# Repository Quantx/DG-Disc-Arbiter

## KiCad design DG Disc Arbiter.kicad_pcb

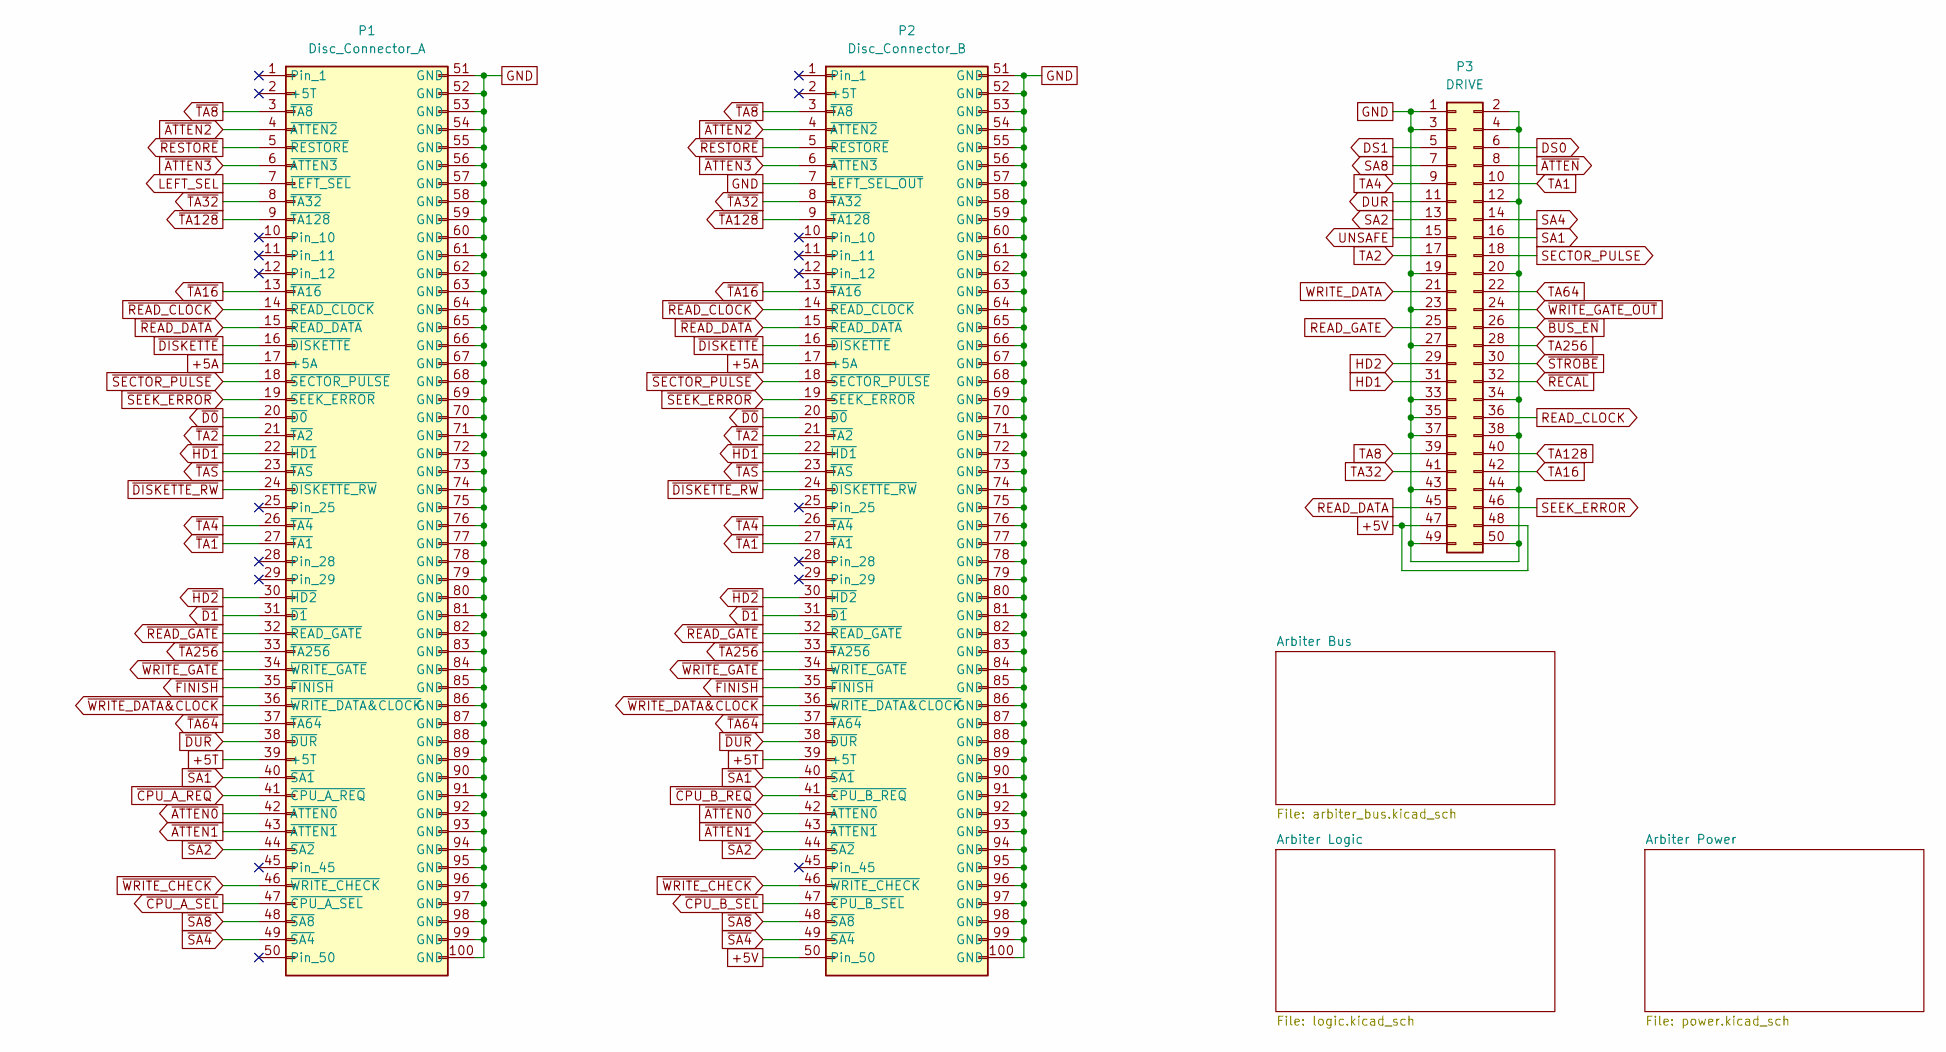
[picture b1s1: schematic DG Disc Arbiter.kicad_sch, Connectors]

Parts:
P1: Disc_Connector_A
P2: Disc_Connector_B
P3: DRIVE

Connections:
unnamed: P1.3 (~TA8), P2.3 (~TA8)
unnamed: P1.4 (~ATTEN2), P2.4 (~ATTEN2)
unnamed: P1.5 (~RESTORE), P2.5 (~RESTORE)
unnamed: P1.6 (~ATTEN3), P2.6 (~ATTEN3)
unnamed: P1.8 (~TA32), P2.8 (~TA32)
unnamed: P1.9 (~TA128), P2.9 (~TA128)
unnamed: P1.13 (~TA16), P2.13 (~TA16)
unnamed: P1.14 (~READ_CLOCK), P2.14 (~READ_CLOCK)
unnamed: P1.15 (~READ_DATA), P2.15 (~READ_DATA)
unnamed: P1.16 (~DISKETTE), P2.16 (~DISKETTE)
unnamed: P1.17 (+5A), P2.17 (+5A)
unnamed: P1.18 (~SECTOR_PULSE), P2.18 (~SECTOR_PULSE)
unnamed: P1.19 (~SEEK_ERROR), P2.19 (~SEEK_ERROR)
unnamed: P1.20 (~D0), P2.20 (~D0)
unnamed: P1.21 (~TA2), P2.21 (~TA2)
unnamed: P1.22 (~HD1), P2.22 (~HD1)
unnamed: P1.23 (~TAS), P2.23 (~TAS)
unnamed: P1.24 (~DISKETTE_RW), P2.24 (~DISKETTE_RW)
unnamed: P1.26 (~TA4), P2.26 (~TA4)
unnamed: P1.27 (~TA1), P2.27 (~TA1)
unnamed: P1.30 (~HD2), P2.30 (~HD2)
unnamed: P1.31 (~D1), P2.31 (~D1)
unnamed: P1.32 (~READ_GATE), P2.32 (~READ_GATE)
unnamed: P1.33 (~TA256), P2.33 (~TA256)
unnamed: P1.34 (~WRITE_GATE), P2.34 (~WRITE_GATE)
unnamed: P1.35 (~FINISH), P2.35 (~FINISH)
unnamed: P1.36 (~WRITE_DATA&CLOCK), P2.36 (~WRITE_DATA&CLOCK)
unnamed: P1.37 (~TA64), P2.37 (~TA64)
unnamed: P1.38 (~DUR), P2.38 (~DUR)
unnamed: P1.39 (+5T), P2.39 (+5T)
unnamed: P1.40 (~SA1), P2.40 (~SA1)
unnamed: P1.42 (~ATTEN0), P2.42 (~ATTEN0)
unnamed: P1.43 (~ATTEN1), P2.43 (~ATTEN1)
unnamed: P1.44 (~SA2), P2.44 (~SA2)
unnamed: P1.46 (~WRITE_CHECK), P2.46 (~WRITE_CHECK)
unnamed: P1.48 (~SA8), P2.48 (~SA8)
unnamed: P1.49 (~SA4), P2.49 (~SA4)
unnamed: P1.51 (GND), P1.52 (GND), P1.53 (GND), P1.54 (GND), P1.55 (GND), P1.56 (GND), P1.57 (GND), P1.58 (GND), P1.59 (GND), P1.60 (GND), P1.61 (GND), P1.62 (GND), P1.63 (GND), P1.64 (GND), P1.65 (GND), P1.66 (GND), P1.67 (GND), P1.68 (GND), P1.69 (GND), P1.70 (GND), P1.71 (GND), P1.72 (GND), P1.73 (GND), P1.74 (GND), P1.75 (GND), P1.76 (GND), P1.77 (GND), P1.78 (GND), P1.79 (GND), P1.80 (GND), P1.81 (GND), P1.82 (GND), P1.83 (GND), P1.84 (GND), P1.85 (GND), P1.86 (GND), P1.87 (GND), P1.88 (GND), P1.89 (GND), P1.90 (GND), P1.91 (GND), P1.92 (GND), P1.93 (GND), P1.94 (GND), P1.95 (GND), P1.96 (GND), P1.97 (GND), P1.98 (GND), P1.99 (GND), P1.100 (GND), P2.7 (~LEFT_SEL_OUT), P2.51 (GND), P2.52 (GND), P2.53 (GND), P2.54 (GND), P2.55 (GND), P2.56 (GND), P2.57 (GND), P2.58 (GND), P2.59 (GND), P2.60 (GND), P2.61 (GND), P2.62 (GND), P2.63 (GND), P2.64 (GND), P2.65 (GND), P2.66 (GND), P2.67 (GND), P2.68 (GND), P2.69 (GND), P2.70 (GND), P2.71 (GND), P2.72 (GND), P2.73 (GND), P2.74 (GND), P2.75 (GND), P2.76 (GND), P2.77 (GND), P2.78 (GND), P2.79 (GND), P2.80 (GND), P2.81 (GND), P2.82 (GND), P2.83 (GND), P2.84 (GND), P2.85 (GND), P2.86 (GND), P2.87 (GND), P2.88 (GND), P2.89 (GND), P2.90 (GND), P2.91 (GND), P2.92 (GND), P2.93 (GND), P2.94 (GND), P2.95 (GND), P2.96 (GND), P2.97 (GND), P2.98 (GND), P2.99 (GND), P2.100 (GND), P3.1, P3.2, P3.3, P3.4, P3.12, P3.19, P3.20, P3.23, P3.27, P3.33, P3.34, P3.35, P3.37, P3.38, P3.43, P3.44, P3.49, P3.50
unnamed: P2.50, P3.47, P3.48

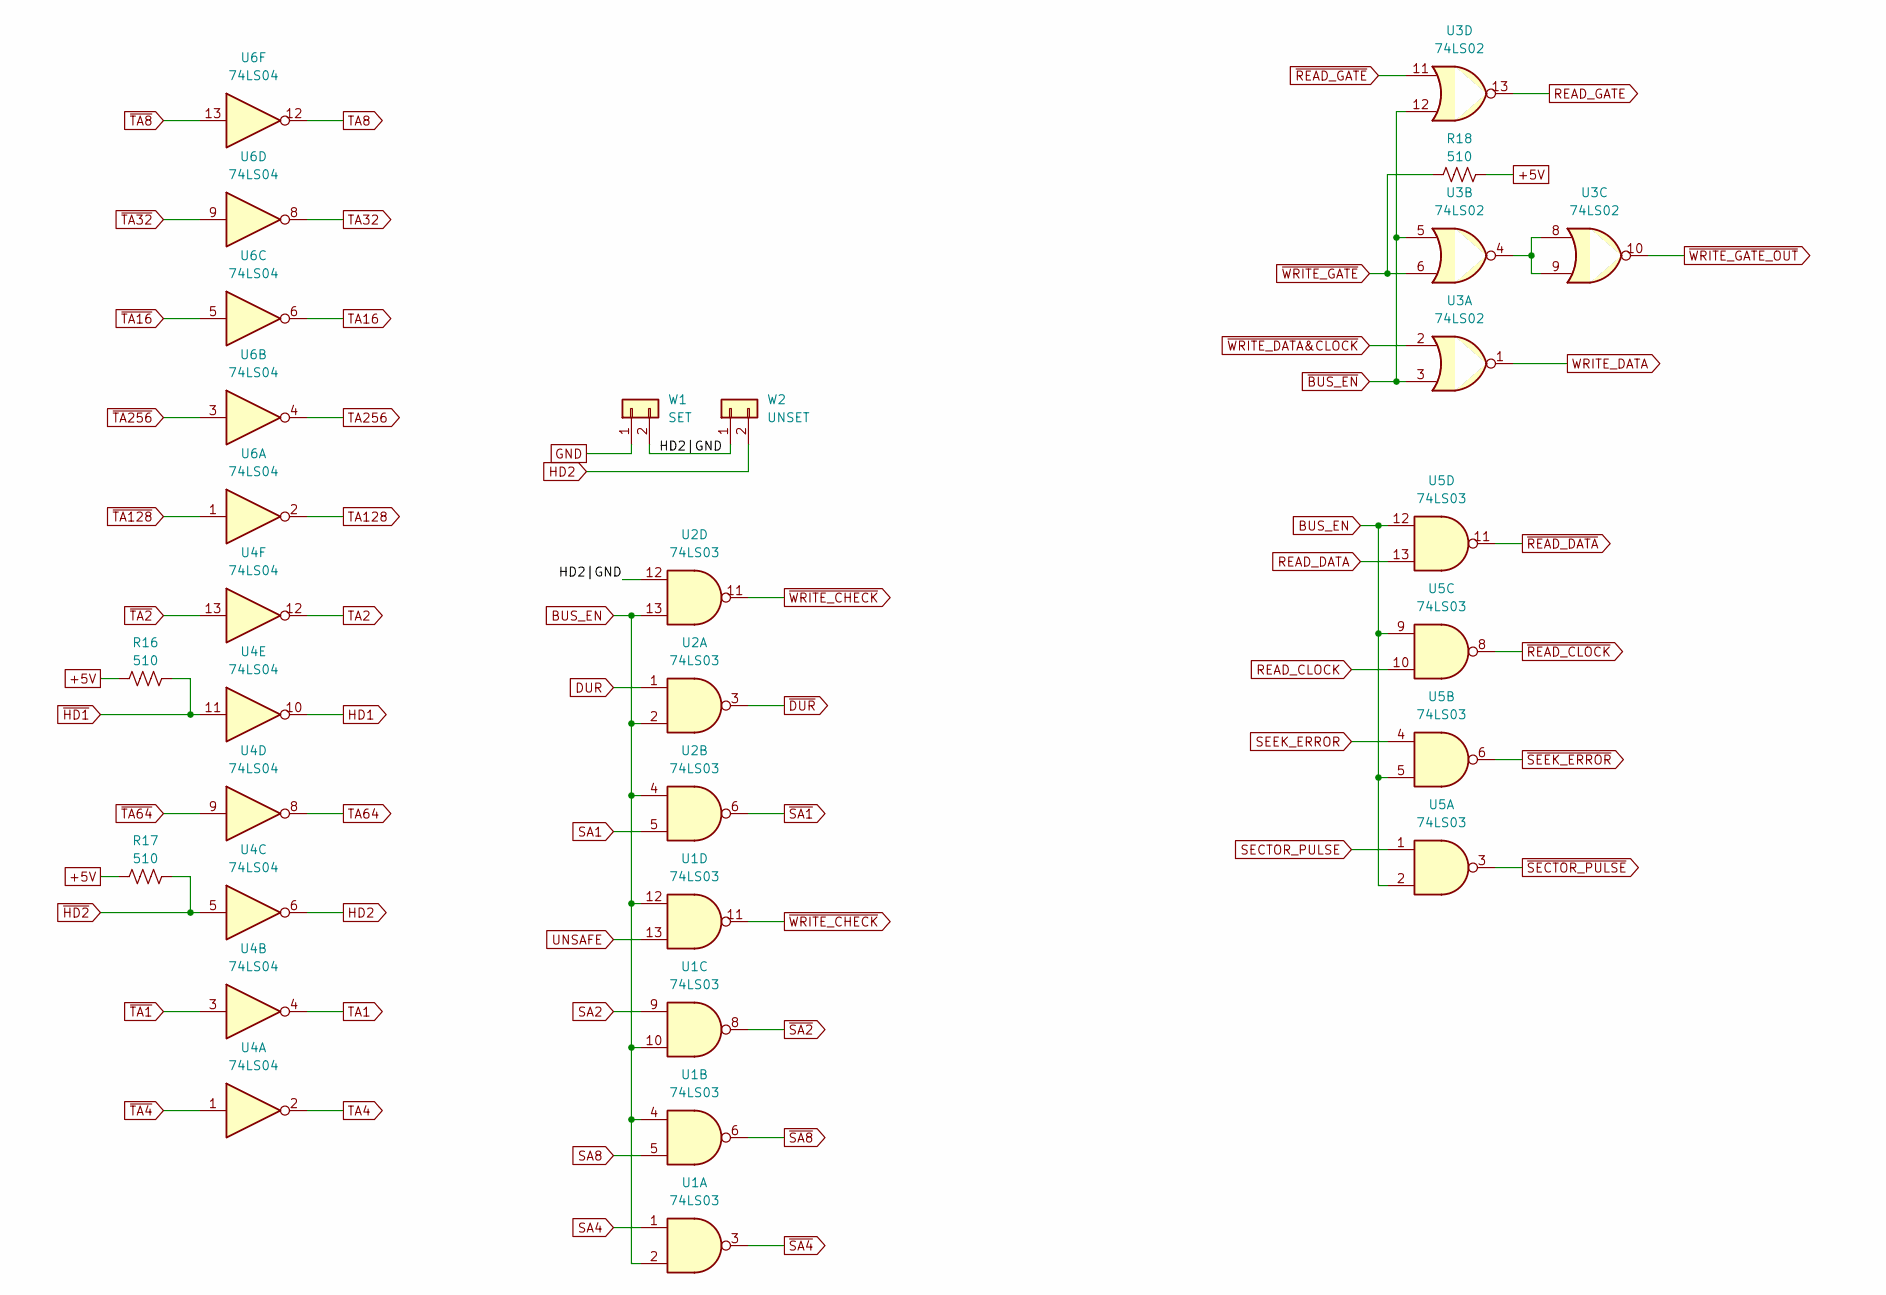
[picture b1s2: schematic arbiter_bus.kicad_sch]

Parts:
R16, R17, R18: 510; R_Axial_DIN0207_L6.3mm_D2.5mm_P15.24mm_Horizontal
U1, U2, U5: 74LS03; DIP-14_W7.62mm_LongPads
U3: 74LS02; DIP-14_W7.62mm_LongPads
U4, U6: 74LS04; DIP-14_W7.62mm_LongPads
W1: SET; PinHeader_1x02_P1.00mm_Vertical
W2: UNSET; PinHeader_1x02_P1.00mm_Vertical

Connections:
+5V: R16.1, R17.1, R18.2; also elsewhere on the board
/Arbiter Bus/HD2|GND: U2.12, W1.2, W2.1
BUS_EN: U1.2, U1.4, U1.10, U1.12, U2.2, U2.4, U2.13, U5.2, U5.5, U5.9, U5.12; also elsewhere on the board
DUR: U2.1
GND: W1.1; also elsewhere on the board
HD1: U4.10
HD2: U4.6, W2.2
unnamed: U3.4, U3.8, U3.9
READ_CLOCK: U5.10
READ_DATA: U5.13
READ_GATE: U3.13
SA1: U2.5
SA2: U1.9
SA4: U1.1
SA8: U1.5
SECTOR_PULSE: U5.1
SEEK_ERROR: U5.4
TA1: U4.4
TA2: U4.12
TA4: U4.2
TA8: U6.12
TA16: U6.6
TA32: U6.8
TA64: U4.8
TA128: U6.2
TA256: U6.4
UNSAFE: U1.13
WRITE_DATA: U3.1
~BUS_EN: U3.3, U3.5, U3.12; also elsewhere on the board
~DUR: U2.3
~HD1: R16.2, U4.11
~HD2: R17.2, U4.5
~READ_CLOCK: U5.8
~READ_DATA: U5.11
~READ_GATE: U3.11
~SA1: U2.6
~SA2: U1.8
~SA4: U1.3
~SA8: U1.6
~SECTOR_PULSE: U5.3
~SEEK_ERROR: U5.6
~TA1: U4.3
~TA2: U4.13
~TA4: U4.1
~TA8: U6.13
~TA16: U6.5
~TA32: U6.9
~TA64: U4.9
~TA128: U6.1
~TA256: U6.3
~WRITE_CHECK: U1.11, U2.11
~WRITE_DATA&CLOCK: U3.2
~WRITE_GATE_OUT: U3.10
~WRITE_GATE: R18.1, U3.6

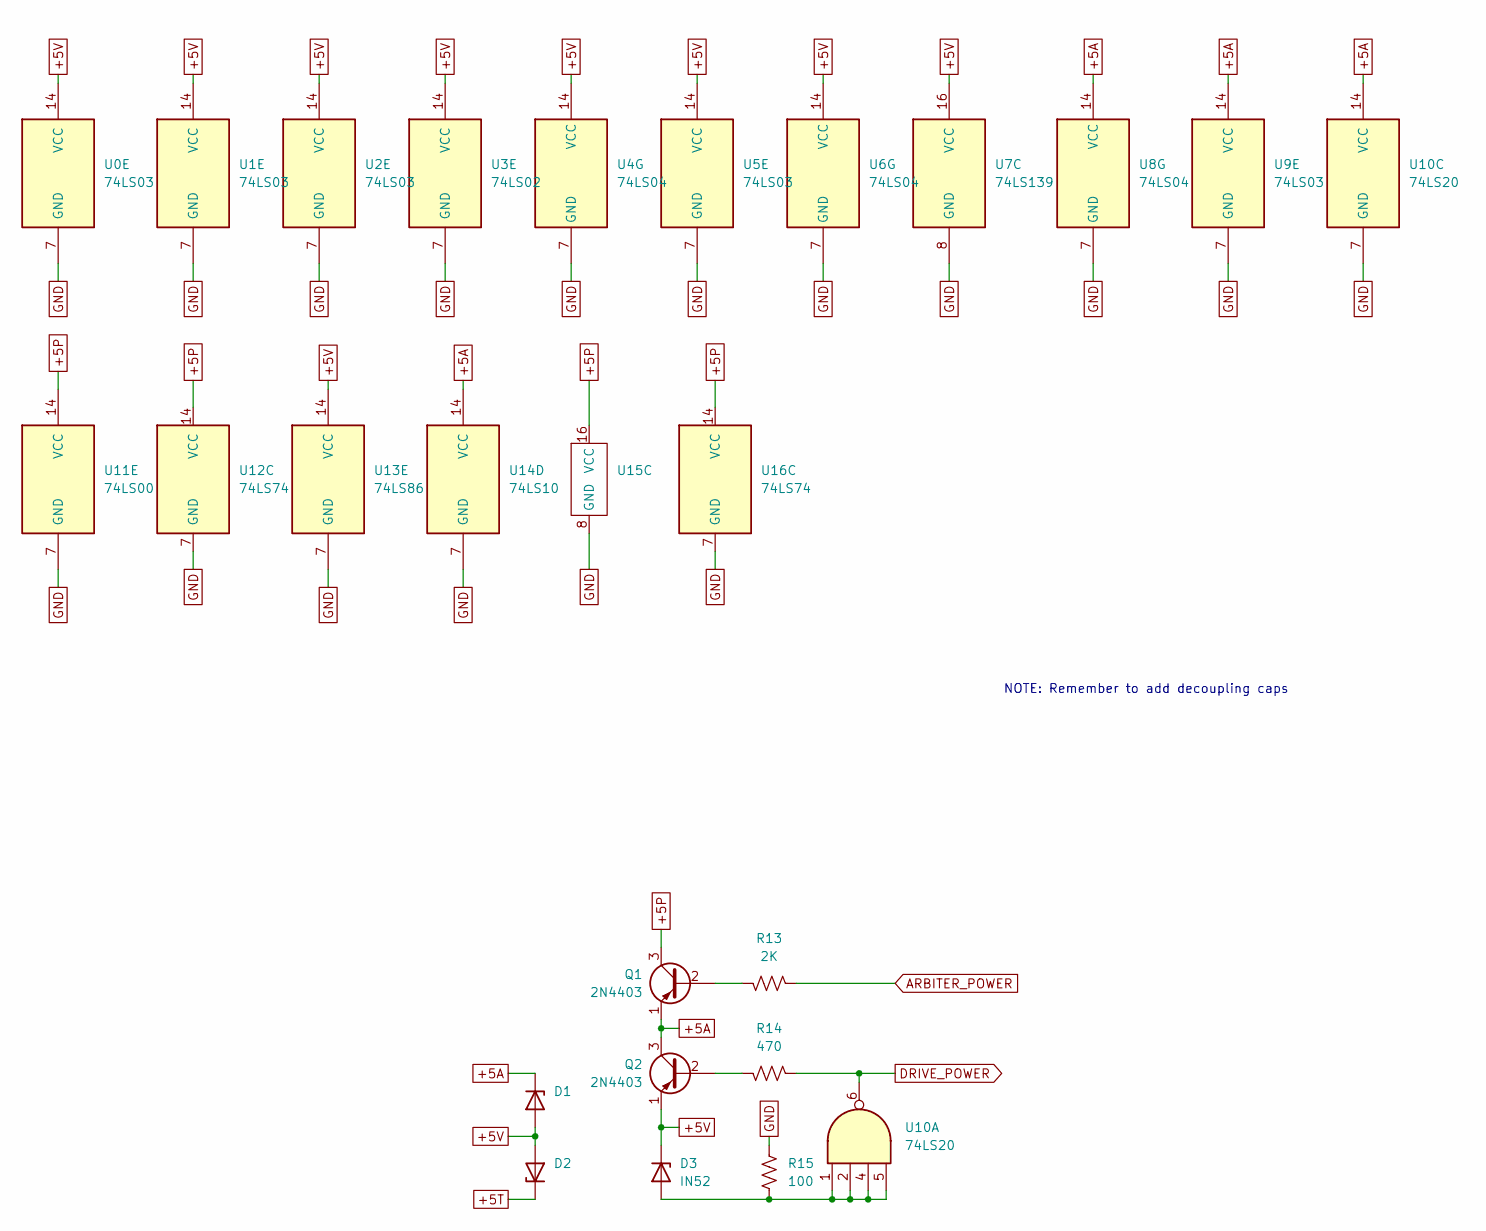
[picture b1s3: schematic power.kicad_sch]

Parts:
D1, D2: D_DO-35_SOD27_P12.70mm_Horizontal
D3: IN52; D_DO-35_SOD27_P12.70mm_Horizontal
Q1, Q2: 2N4403; TO-92
R13: 2K; R_Axial_DIN0207_L6.3mm_D2.5mm_P15.24mm_Horizontal
R14: 470; R_Axial_DIN0207_L6.3mm_D2.5mm_P15.24mm_Horizontal
R15: 100; R_Axial_DIN0207_L6.3mm_D2.5mm_P15.24mm_Horizontal
U0, U1, U2, U5, U9: 74LS03; DIP-14_W7.62mm_LongPads
U3: 74LS02; DIP-14_W7.62mm_LongPads
U4, U6, U8: 74LS04; DIP-14_W7.62mm_LongPads
U7: 74LS139; DIP-16_W7.62mm_LongPads
U10: 74LS20; DIP-14_W7.62mm_LongPads
U11: 74LS00; DIP-14_W7.62mm_LongPads
U12, U16: 74LS74; DIP-14_W7.62mm_LongPads
U13: 74LS86; DIP-14_W7.62mm_LongPads
U14: 74LS10; DIP-14_W7.62mm_LongPads
U15: (no value)

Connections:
+5A: D1.1 (K), Q1.1 (E), Q2.3 (C), U8.14 (VCC), U9.14 (VCC), U10.14 (VCC), U14.14 (VCC)
+5P: Q1.3 (C), U11.14 (VCC), U12.14 (VCC), U15.16 (VCC), U16.14 (VCC); also elsewhere on the board
+5T: D2.1 (K); also elsewhere on the board
+5V: D1.2 (A), D2.2 (A), D3.1 (K), Q2.1 (E), U0.14 (VCC), U1.14 (VCC), U2.14 (VCC), U3.14 (VCC), U4.14 (VCC), U5.14 (VCC), U6.14 (VCC), U7.16 (VCC), U13.14 (VCC); also elsewhere on the board
ARBITER_POWER: R13.1; also elsewhere on the board
DRIVE_POWER: R14.1, U10.6; also elsewhere on the board
GND: R15.1, U0.7 (GND), U1.7 (GND), U2.7 (GND), U3.7 (GND), U4.7 (GND), U5.7 (GND), U6.7 (GND), U7.8 (GND), U8.7 (GND), U9.7 (GND), U10.7 (GND), U11.7 (GND), U12.7 (GND), U13.7 (GND), U14.7 (GND), U15.8 (GND), U16.7 (GND); also elsewhere on the board
unnamed: D3.2 (A), R15.2, U10.1, U10.2, U10.4, U10.5
unnamed: Q1.2 (B), R13.2
unnamed: Q2.2 (B), R14.2

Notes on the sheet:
NOTE: Remember to add decoupling caps

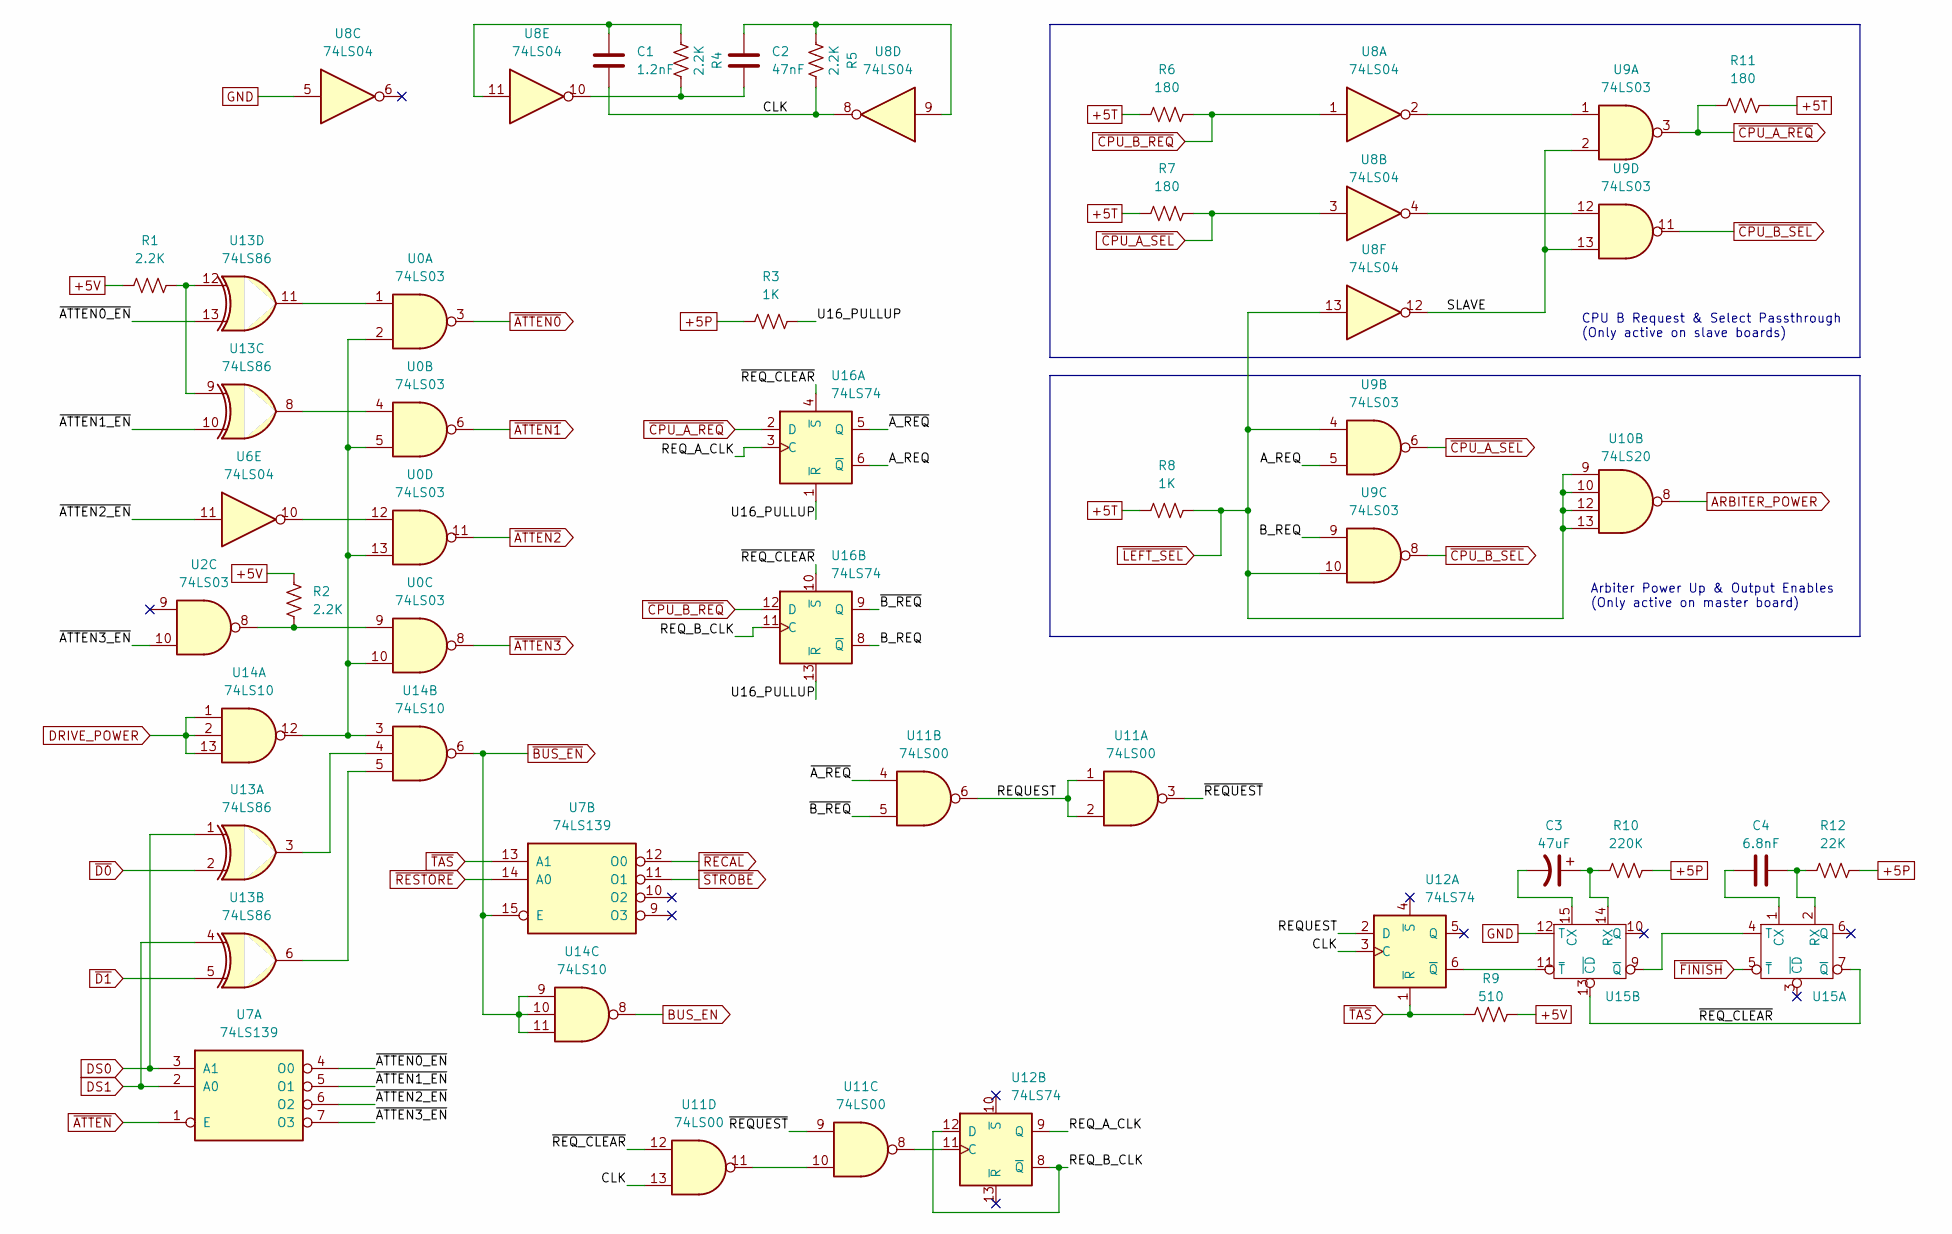
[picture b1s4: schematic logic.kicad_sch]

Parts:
C1: 1.2nF; C_Axial_L3.8mm_D2.6mm_P12.50mm_Horizontal
C2: 47nF; C_Axial_L3.8mm_D2.6mm_P12.50mm_Horizontal
C3: 47uF
C4: 6.8nF; C_Axial_L3.8mm_D2.6mm_P12.50mm_Horizontal
R1, R2, R4, R5: 2.2K; R_Axial_DIN0207_L6.3mm_D2.5mm_P15.24mm_Horizontal
R3, R8: 1K; R_Axial_DIN0207_L6.3mm_D2.5mm_P15.24mm_Horizontal
R6, R7, R11: 180; R_Axial_DIN0207_L6.3mm_D2.5mm_P15.24mm_Horizontal
R9: 510; R_Axial_DIN0207_L6.3mm_D2.5mm_P15.24mm_Horizontal
R10: 220K; R_Axial_DIN0207_L6.3mm_D2.5mm_P15.24mm_Horizontal
R12: 22K; R_Axial_DIN0207_L6.3mm_D2.5mm_P15.24mm_Horizontal
U0, U2, U9: 74LS03; DIP-14_W7.62mm_LongPads
U6, U8: 74LS04; DIP-14_W7.62mm_LongPads
U7: 74LS139; DIP-16_W7.62mm_LongPads
U10: 74LS20; DIP-14_W7.62mm_LongPads
U11: 74LS00; DIP-14_W7.62mm_LongPads
U12, U16: 74LS74; DIP-14_W7.62mm_LongPads
U13: 74LS86; DIP-14_W7.62mm_LongPads
U14: 74LS10; DIP-14_W7.62mm_LongPads
U15: (no value)

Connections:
+5P: R3.1, R10.2, R12.2; also elsewhere on the board
+5T: R6.1, R7.1, R8.1, R11.2; also elsewhere on the board
+5V: R1.1, R2.1, R9.2; also elsewhere on the board
/Arbiter Logic/A_REQ: U9.5, U16.6 (~Q)
/Arbiter Logic/B_REQ: U9.9, U16.8 (~Q)
/Arbiter Logic/CLK: C1.2, R5.2, U8.8, U11.13, U12.3 (C)
/Arbiter Logic/REQUEST: U11.1, U11.2, U11.6, U12.2 (D)
/Arbiter Logic/REQ_A_CLK: U12.9 (Q), U16.3 (C)
/Arbiter Logic/REQ_B_CLK: U12.8 (~Q), U12.12 (D), U16.11 (C)
/Arbiter Logic/SLAVE: U8.12, U9.2, U9.13
/Arbiter Logic/U16_PULLUP: R3.2, U16.1 (~R), U16.13 (~R)
/Arbiter Logic/~ATTEN0_EN: U7.4 (O0), U13.13
/Arbiter Logic/~ATTEN1_EN: U7.5 (O1), U13.10
/Arbiter Logic/~ATTEN2_EN: U6.11, U7.6 (O2)
/Arbiter Logic/~ATTEN3_EN: U2.10, U7.7 (O3)
/Arbiter Logic/~A_REQ: U11.4, U16.5 (Q)
/Arbiter Logic/~B_REQ: U11.5, U16.9 (Q)
/Arbiter Logic/~REQUEST: U11.3, U11.9
/Arbiter Logic/~REQ_CLEAR: U11.12, U15.7 (~Q), U15.13 (~CD), U16.4 (~S), U16.10 (~S)
ARBITER_POWER: U10.8; also elsewhere on the board
BUS_EN: U14.8; also elsewhere on the board
DRIVE_POWER: U14.1, U14.2, U14.13; also elsewhere on the board
DS0: U7.3 (A1), U13.1
DS1: U7.2 (A0), U13.4
GND: U8.5, U15.12 (T); also elsewhere on the board
unnamed: C1.1, R4.1, U8.11
unnamed: C2.1, R5.1, U8.9
unnamed: C2.2, R4.2, U8.10
unnamed: C3.1, R10.1, U15.14 (RX)
unnamed: C3.2, U15.15 (CX)
unnamed: C4.1, R12.1, U15.2 (RX)
unnamed: C4.2, U15.1 (CX)
unnamed: R1.2, U13.9, U13.12
unnamed: R2.2, U0.9, U2.8
unnamed: U0.1, U13.11
unnamed: U0.4, U13.8
unnamed: U0.2, U0.5, U0.10, U0.13, U14.3, U14.12
unnamed: U0.12, U6.10
unnamed: U8.2, U9.1
unnamed: U8.4, U9.12
unnamed: U11.8, U12.11 (C)
unnamed: U11.10, U11.11
unnamed: U12.6 (~Q), U15.11 (~T)
unnamed: U13.3, U14.4
unnamed: U13.6, U14.5
unnamed: U15.4 (T), U15.9 (~Q)
~ATTEN0: U0.3
~ATTEN1: U0.6
~ATTEN2: U0.11
~ATTEN3: U0.8
~ATTEN: U7.1 (E)
~BUS_EN: U7.15 (E), U14.6, U14.9, U14.10, U14.11; also elsewhere on the board
~CPU_A_REQ: R11.1, U9.3, U16.2 (D)
~CPU_A_SEL: R7.2, U8.3, U9.6
~CPU_B_REQ: R6.2, U8.1, U16.12 (D)
~CPU_B_SEL: U9.8, U9.11
~D0: U13.2
~D1: U13.5
~FINISH: U15.5 (~T)
~LEFT_SEL: R8.2, U8.13, U9.4, U9.10, U10.9, U10.10, U10.12, U10.13
~RECAL: U7.12 (O0)
~RESTORE: U7.14 (A0)
~STROBE: U7.11 (O1)
~TAS: R9.1, U7.13 (A1), U12.1 (~R)

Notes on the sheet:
CPU B Request & Select Passthrough (Only active on slave boards)
Arbiter Power Up & Output Enables (Only active on master board)

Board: 2 copper layers, 45 parts (0 on the bottom side), 63 nets, no tracks yet.

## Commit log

2022-09-30 Removed backups
